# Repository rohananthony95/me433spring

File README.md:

# ME433spring
## Overview
This repository contains the documentation for assignments in Mechanical Engineering 433: Advanced mechatronics. Over the course of the quarter I learned a variety of skills including circuit board design, communication protocols and familiarized myself with sophisticated software and hardware platforms. I eventually used all of these skills to design a mobile robot which used visual data to follow a path. 
### Couse Info
Professor: Nick Marchuk
Course Page: [ME 433](https://github.com/ndm736/ME433_2018/wiki)
### Hardware
[PIC32MX250 Microcontroller](http://ww1.microchip.com/downloads/en/DeviceDoc/PIC32MX1XX2XX-28-36-44-PIN-DS60001168K.pdf),
[MCP1702 Voltage Regulator](http://ww1.microchip.com/downloads/en/DeviceDoc/22008E.pdf),
[8MHz crystal resonator](https://www.digikey.com/products/en?keywords=490-1212-ND),
[USB breakout board](https://www.pololu.com/product/2593),
[TFT LCD](https://www.aliexpress.com/item/Free-Shipping-1-8-inch-TFT-touch-LCD-Module-LCD-Screen-Module-SPI-serial-51-drivers/32263827143.html),
[I/O Expander](http://ww1.microchip.com/downloads/en/DeviceDoc/21919e.pdf),
[IMU](https://www.pololu.com/product/2736),
[Android Phone](https://www.amazon.com/gp/product/B00HPP3VW2/ref=oh_aui_detailpage_o00_s00?ie=UTF8&psc=1)
### Tools
Eagle, Onshape
### Languages
C, Java, Matlab
## HW1
In the first assignment I familiarized myself with the PIC32 microcontroller and its peripheral components and assembled a general puropose circuit board for the coming assignments. The ojective of the assignment was to build our circuit board and demonstrate that it could make an LED blink at a frequency of 1kHz. [HW1 assignment description](https://github.com/ndm736/ME433_2018/wiki/HW1).

## HW2
In the second assignment I designed an EAGLE schematic of the final circuit board. [HW2 assignment description](https://github.com/ndm736/ME433_2018/wiki/HW2).

## HW3
Designed PCB and generated Gerber files. [HW3 assignment description](https://github.com/ndm736/ME433_2018/wiki/HW3).
## HW4
In the fourth assignment I added an SPI DAC to our original circuit board configuration. I created functions to initialize and communicate with the DAC. The DAC output both a sine wave as well as a triangle wave. [HW4 assignment description](https://github.com/ndm736/ME433_2018/wiki/HW4). 

## HW5
Here I incorporated an pin expander to my breadboard and communicated to it using the I2C protocol. [HW5 assignment description](https://github.com/ndm736/ME433_2018/wiki/HW5).
[HW5 demo download](https://minhaskamal.github.io/DownGit/#/home?url=https://github.com/rohananthony95/me433spring/blob/master/HW5/HW5.MOV).
## HW6
In this assignment I added an LCD module to my circuit board and communicated with it using SPI. [HW6 assignment description](https://github.com/ndm736/ME433_2018/wiki/HW6).
[HW6 demo download](https://minhaskamal.github.io/DownGit/#/home?url=https://github.com/rohananthony95/me433spring/blob/master/HW6/HW6.mov).
## HW7
I added an I2C accelerometer to the board and wrote a program that displayed the orientation of the board on the LCD. [HW7 assignment description](https://github.com/ndm736/ME433_2018/wiki/HW7).
[HW7 demo download](https://minhaskamal.github.io/DownGit/#/home?url=https://github.com/rohananthony95/me433spring/blob/master/HW7/HW7.MOV).
## HW8
The objective here was to implement the previous assignment in MPLABX Harmony. [HW8 assignment description](https://github.com/ndm736/ME433_2018/wiki/HW9).
## HW9
The goal of this assignment was to configure the microcontroller to communicate with my computer using USB. [HW9 assignment description](https://github.com/ndm736/ME433_2018/wiki/HW9).
[HW9 demo download](https://minhaskamal.github.io/DownGit/#/home?url=https://github.com/rohananthony95/me433spring/blob/master/HW9/HW9.MOV).
## HW10
I analyzed the gyroscope data sent to the computer via USB with FIR, IIR, and MAV filters. [HW10 assignment description](https://github.com/ndm736/ME433_2018/wiki/HW10).

## HW11
The objective of this assignment was to control the cursor of my computer with the gyroscope of my circuit board. [HW11 assignment description](https://github.com/ndm736/ME433_2018/wiki/HW11).
[HW11 demo download](https://minhaskamal.github.io/DownGit/#/home?url=https://github.com/rohananthony95/me433spring/blob/master/HW11/HW11.MOV).
## HW12
Here I familiarized myself with Android and wrote a simple application with a clean interface and basic modules like a slider.
[HW12 assignment description](https://github.com/ndm736/ME433_2018/wiki/HW12).
## HW13
I wrote an Android application that could recognize green objects in the field of view of the camera. 
[HW13 assignment description](https://github.com/ndm736/ME433_2018/wiki/HW13).
[HW13 demo download](https://minhaskamal.github.io/DownGit/#/home?url=https://github.com/rohananthony95/me433spring/blob/master/HW13/HW13.MOV).
## HW14
The purpose of this assignment was to make an Android application which could send data to the microcontroller and have that data returned back to the application demonstrating communication using USB. [HW14 assignment description](https://github.com/ndm736/ME433_2018/wiki/HW14).
[HW14 demo download](https://minhaskamal.github.io/DownGit/#/home?url=https://github.com/rohananthony95/me433spring/blob/master/HW14/HW14.MOV).
## HW15
I created a base and wheels for the robot using CAD. I 3D printed the wheels and laser cut the frame of the robot using acrylic. [HW15 assignment description]
(https://github.com/ndm736/ME433_2018/wiki/HW15).

## HW16
Wrote a simple PI controller for the wheel velocity of my robot. [HW16 assignment description](https://github.com/ndm736/ME433_2018/wiki/HW16).
## HW17
Wrote the Android application to find the center of a rainbow line. [HW17 assignment description](https://github.com/ndm736/ME433_2018/wiki/HW17).
## HW18
Combined all of the components and had a finished robot which followed a rainbow path. [HW18 assignment description](https://github.com/ndm736/ME433_2018/wiki/HW18).

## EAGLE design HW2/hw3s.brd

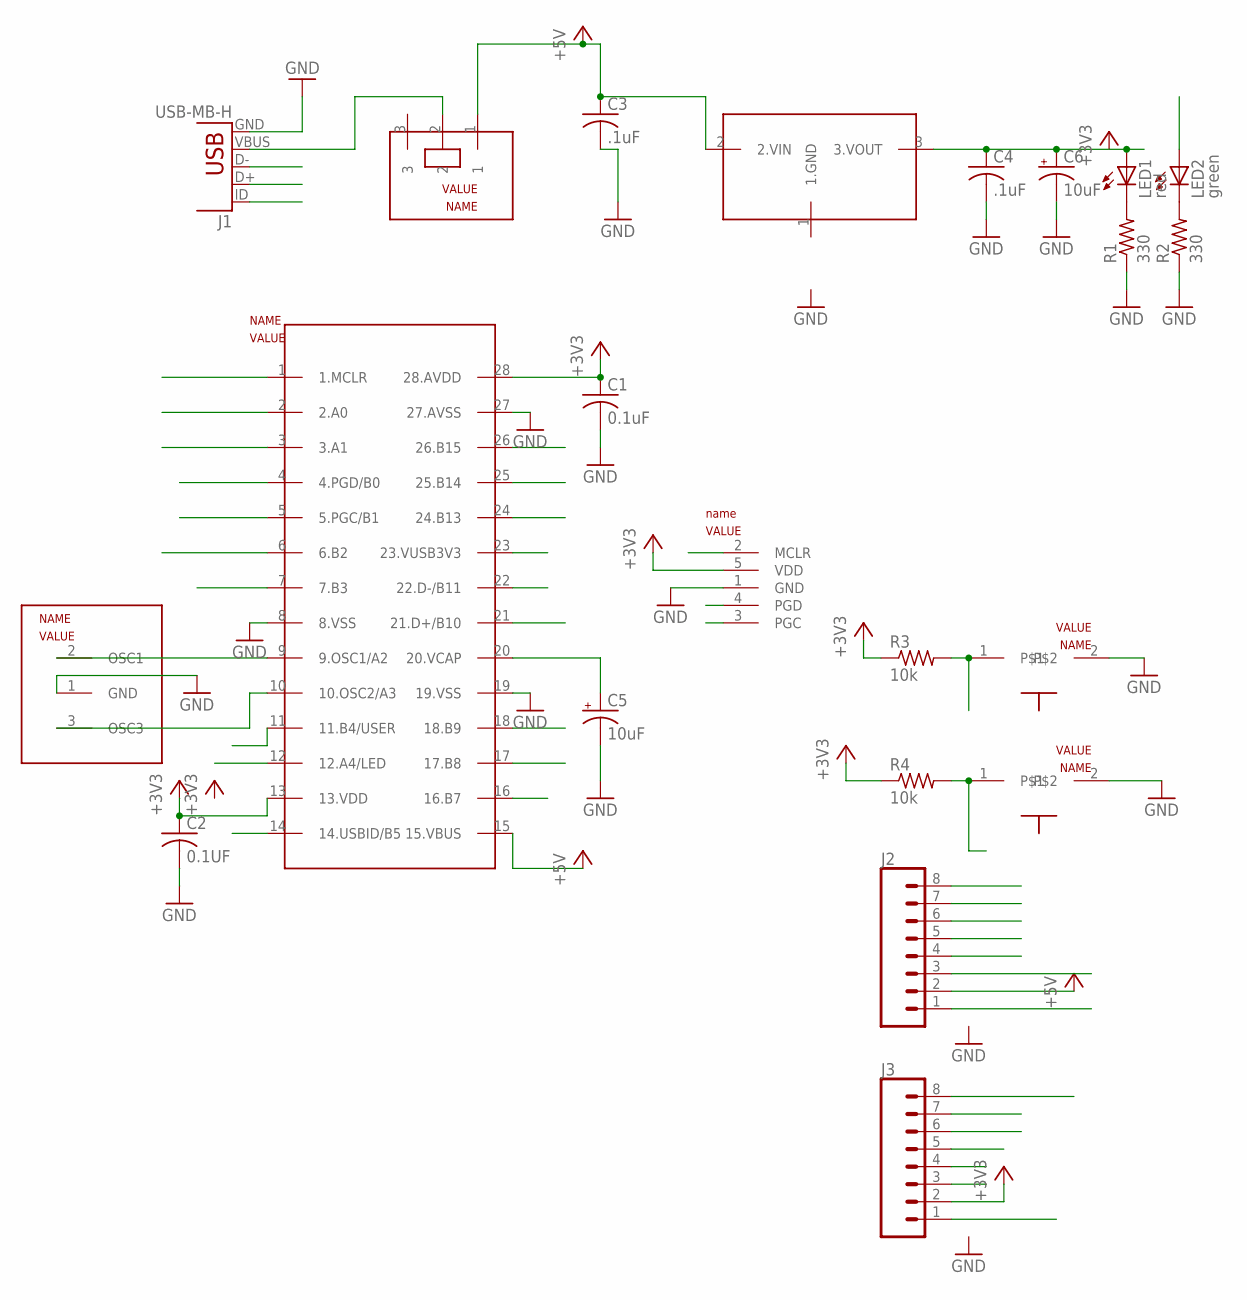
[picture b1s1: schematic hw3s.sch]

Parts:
C1: 0.1uF; C025-025X050
C2: 0.1UF; C025-025X050
C3, C4: .1uF; C025-025X050
C5, C6: 10uF; B45181B
J1: USB-MB-H
J2, J3: CONN_08"; 1X08
LED1: red; LED3MM
LED2: green; LED3MM
R1, R2: 330; 0207/10
R3, R4: 10k; 0207/10
U$1: PIC32; DIL28-3
U$2: SLIDE
U$3: MCP1702; TO92
U$4: RESET; PB
U$5: USER; PB
U$6: PICKIT3; 1X05
U$7: 8MHZ; OSC

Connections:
+3V3: C1.1, C2.1, J3.2, R3.1, R4.1, U$1.13 (13.VDD), U$1.28 (28.AVDD), U$6.5 (VDD)
+5V: C3.1, J2.2, U$1.15 (15.VBUS), U$2.1, U$3.2 (2.VIN)
A0: J3.8, U$1.2 (2.A0)
A1: J3.7, U$1.3 (3.A1)
A4/LED: J3.3, LED2.A, U$1.12 (12.A4/LED)
B2: J3.6, U$1.6 (6.B2)
B3: J3.5, U$1.7 (7.B3)
B4/USER: J3.4, R4.2, U$1.11 (11.B4/USER), U$5.1
B7: J2.3, U$1.16 (16.B7)
B8: J2.4, U$1.17 (17.B8)
B9: J2.5, U$1.18 (18.B9)
B13: J2.6, U$1.24 (24.B13)
B14: J2.7, U$1.25 (25.B14)
B15: J2.8, U$1.26 (26.B15)
B+/B10: J1.D+
D+/B10: U$1.21 (21.D+/B10)
D-/B11: J1.D-, U$1.22 (22.D-/B11)
GND: C1.2, C2.2, C3.2, C4.2, C5.-, C6.-, J1.GND, R1.1, R2.1, U$1.8 (8.VSS), U$1.19 (19.VSS), U$1.27 (27.AVSS), U$4.2, U$5.2, U$6.1 (GND), U$7.1 (GND)
MCLR: R3.2, U$1.1 (1.MCLR), U$4.1, U$6.2 (MCLR)
unnamed: J1.VBUS, U$2.2
unnamed: U$1.9 (9.OSC1/A2), U$7.2 (OSC1)
unnamed: C4.1, C6.+, LED1.A, U$3.3 (3.VOUT)
unnamed: LED1.K (C), R1.2
unnamed: LED2.K (C), R2.2
unnamed: U$1.10 (10.OSC2/A3), U$7.3 (OSC3)
unnamed: C5.+, U$1.20 (20.VCAP)
PGC/B1: U$1.5 (5.PGC/B1), U$6.3 (PGC)
PGD/B0: U$1.4 (4.PGD/B0), U$6.4 (PGD)
USBID/B5: J1.ID, U$1.14 (14.USBID/B5)
VUSB3V3: U$1.23 (23.VUSB3V3)

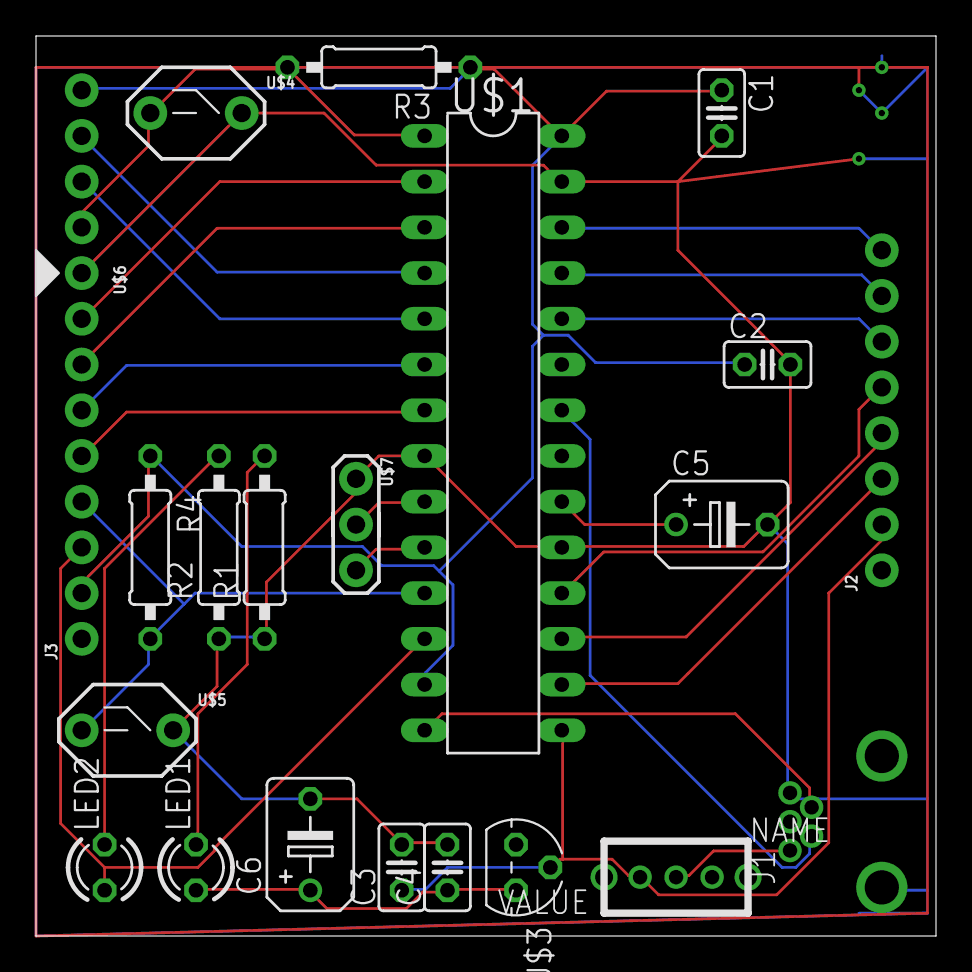
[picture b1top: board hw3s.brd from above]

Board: 2 copper layers, 50.0 x 50.0 mm, 22 parts (0 on the bottom side), 27 nets.

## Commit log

2018-04-26 first commit
    init
2018-04-26 test
2018-04-26 moving stuff around
2018-04-26 edits
2018-04-29 start6
2018-05-07 final
2018-05-29 added matlab
2018-06-06 hw14
2018-06-10 hw15
2018-06-17 red dot
2018-06-17 error
2018-11-07 reorganization
2018-11-07 README.md
2019-01-09 videos
2019-01-09 hw3s
2019-01-09 hw9mov
2019-01-09 hw13
2019-01-09 moving
2019-01-09 hw10
2019-01-09 frame
